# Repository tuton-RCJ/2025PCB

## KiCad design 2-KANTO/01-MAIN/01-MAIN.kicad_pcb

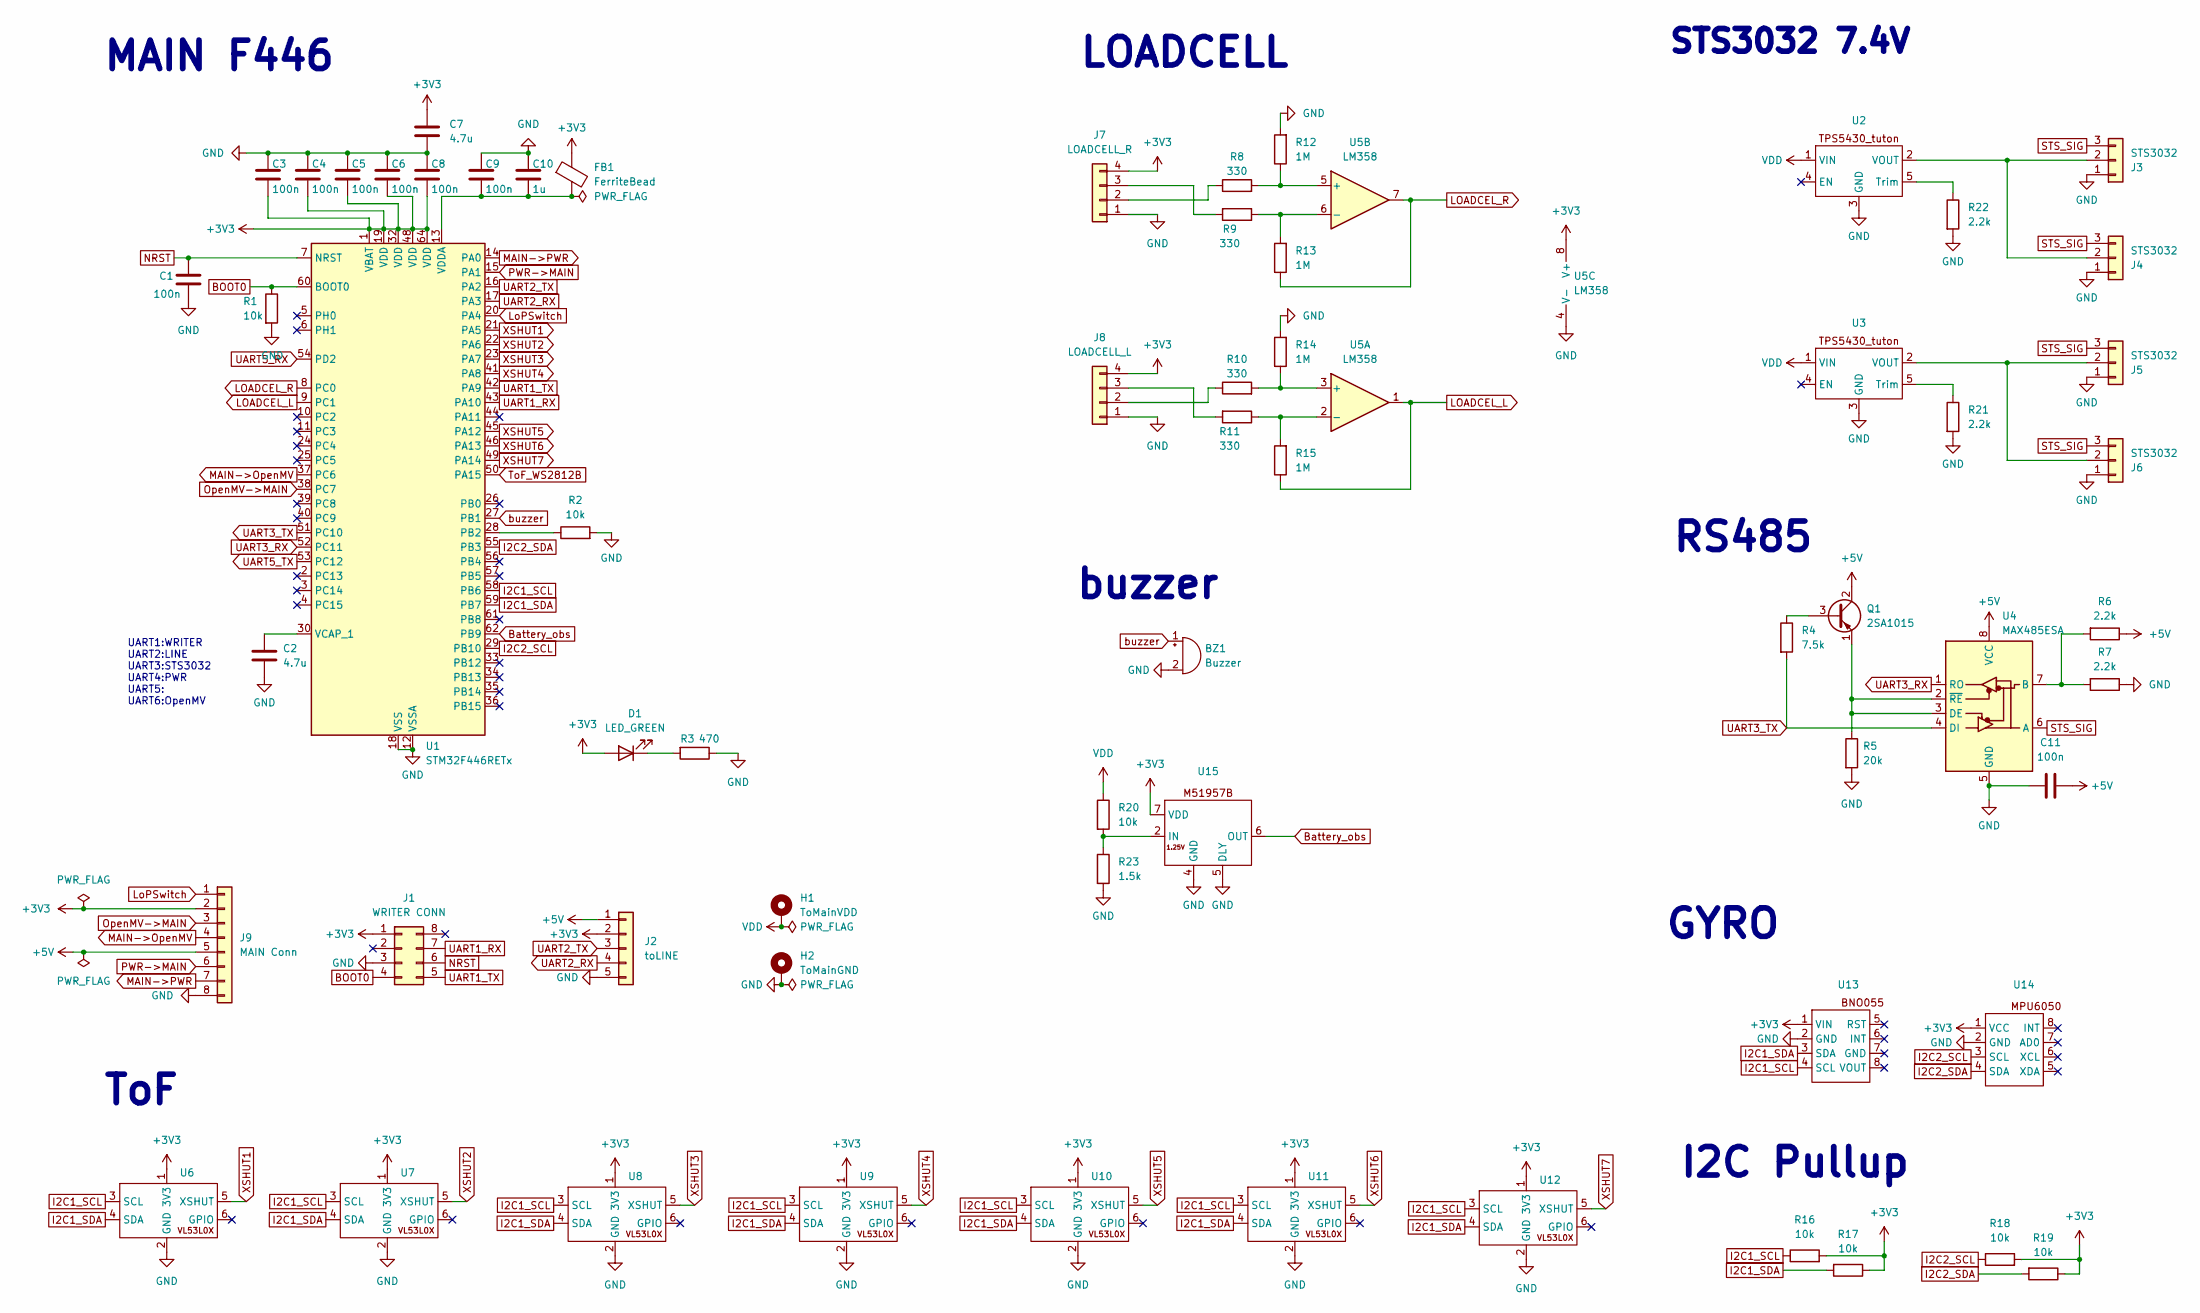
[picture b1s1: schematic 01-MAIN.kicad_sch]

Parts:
BZ1: Buzzer; Buzzer_TDK_PS1240P02BT_D12.2mm_H6.5mm
C1, C3, C4, C5, C6, C8, C9, C11: 100n; C_0402_1005Metric; LCSC C1525
C2, C7: 4.7u; C_0402_1005Metric; LCSC C23733
C10: 1u; C_0402_1005Metric; LCSC C52923
D1: LED_GREEN; LED_0805_2012Metric; LCSC C2297
FB1: FerriteBead; R_0805_2012Metric; LCSC C1015
H1: ToMainVDD; MountingHole_3.2mm_M3_Pad_Via
H2: ToMainGND; MountingHole_3.2mm_M3_Pad_Via
J1: WRITER CONN; PinSocket_2x04_P2.54mm_Horizontal
J2: toLINE; JST_XH_B5B-XH-A_1x05_P2.50mm_Vertical
J3, J4, J5, J6: STS3032; Molex_SPOX_5267-03A_1x03_P2.50mm_Vertical
J7: LOADCELL_R; JST_XH_B4B-XH-A_1x04_P2.50mm_Vertical
J8: LOADCELL_L; JST_XH_B4B-XH-A_1x04_P2.50mm_Vertical
J9: MAIN Conn; JST_XH_B8B-XH-A_1x08_P2.50mm_Vertical
Q1: 2SA1015; TO-92_Inline
R1, R2, R16, R17, R18, R19, R20: 10k; R_0603_1608Metric; LCSC C25804
R3: 470; R_0603_1608Metric; LCSC C23179
R4: 7.5k; R_0603_1608Metric; LCSC C23234
R5: 20k; R_0603_1608Metric; LCSC C4184
R6, R7, R21, R22: 2.2k; R_0603_1608Metric; LCSC C4190
R8, R9, R10, R11: 330; R_0603_1608Metric; LCSC C23138
R12, R13, R14, R15: 1M; R_0603_1608Metric; LCSC C22935
R23: 1.5k; R_0603_1608Metric; LCSC C22843
U1: STM32F446RETx; LQFP-64_10x10mm_P0.5mm; LCSC C69336
U2, U3: PinHeader_1x05_P2.54mm_Vertical
U4: MAX485ESA; SOP-8_3.9x4.9mm_P1.27mm; LCSC C668206
U5: LM358; SOIC-8_3.9x4.9mm_P1.27mm; LCSC C5423
U6, U7, U8, U9, U10, U11, U12: vl53l0x_vertical
U13: BNO055
U14: MPU6050
U15: M51957B

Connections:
+3V3: C3.2, C4.2, C5.2, C6.2, C7.1, C8.2, D1.2 (A), FB1.1, J1.1, J2.2, J7.4, J8.4, J9.2, R16.2, R17.1, R18.2, R19.1, U1.1 (VBAT), U1.19 (VDD), U1.32 (VDD), U1.48 (VDD), U1.64 (VDD), U5.8 (V+), U6.1 (3V3), U7.1 (3V3), U8.1 (3V3), U9.1 (3V3), U10.1 (3V3), U11.1 (3V3), U12.1 (3V3), U13.1 (VIN), U14.1 (VCC), U15.7 (VDD)
+5V: C11.1, J2.1, J9.5, Q1.2 (C), R6.1, U4.8 (VCC)
BOOT0: J1.4, R1.1, U1.60 (BOOT0)
Battery_obs: U1.62 (PB9), U15.6 (OUT)
GND: BZ1.2 (+), C1.1, C2.2, C3.1, C4.1, C5.1, C6.1, C7.2, C8.1, C9.1, C10.1, C11.2, H2.1, J1.3, J2.5, J3.1, J4.1, J5.1, J6.1, J7.1, J8.1, J9.8, R1.2, R2.2, R3.1, R5.2, R7.1, R12.2, R14.2, R21.2, R22.2, R23.2, U1.12 (VSSA), U1.18 (VSS), U1.31 (VSS), U1.47 (VSS), U1.63 (VSS), U2.3 (GND), U3.3 (GND), U4.5 (GND), U5.4 (V-), U6.2 (GND), U7.2 (GND), U8.2 (GND), U9.2 (GND), U10.2 (GND), U11.2 (GND), U12.2 (GND), U13.2 (GND), U14.2 (GND), U15.4 (GND), U15.5 (DLY)
I2C1_SCL: R16.1, U1.58 (PB6), U6.3 (SCL), U7.3 (SCL), U8.3 (SCL), U9.3 (SCL), U10.3 (SCL), U11.3 (SCL), U12.3 (SCL), U13.4 (SCL)
I2C1_SDA: R17.2, U1.59 (PB7), U6.4 (SDA), U7.4 (SDA), U8.4 (SDA), U9.4 (SDA), U10.4 (SDA), U11.4 (SDA), U12.4 (SDA), U13.3 (SDA)
I2C2_SCL: R18.1, U1.29 (PB10), U14.3 (SCL)
I2C2_SDA: R19.2, U1.55 (PB3), U14.4 (SDA)
LOADCEL_L: R15.1, U1.9 (PC1), U5.1
LOADCEL_R: R13.1, U1.8 (PC0), U5.7
LoPSwitch: J9.1, U1.20 (PA4)
MAIN->OpenMV: J9.4, U1.37 (PC6)
MAIN->PWR: J9.7, U1.14 (PA0)
NRST: C1.2, J1.6, U1.7 (NRST)
unnamed: D1.1 (K), R3.2
unnamed: J3.2, J4.2, U2.2 (VOUT)
unnamed: J5.2, J6.2, U3.2 (VOUT)
unnamed: J7.2, R8.1
unnamed: J7.3, R9.2
unnamed: J8.2, R10.1
unnamed: J8.3, R11.2
unnamed: Q1.3 (B), R4.1
unnamed: Q1.1 (E), R5.1, U4.2 (~RE), U4.3 (DE)
unnamed: R2.1, U1.28 (PB2)
unnamed: C2.1, U1.30 (VCAP_1)
unnamed: C9.2, C10.2, FB1.2, U1.13 (VDDA)
unnamed: R22.1, U2.5 (Trim)
unnamed: R21.1, U3.5 (Trim)
unnamed: R6.2, R7.2, U4.7 (B)
unnamed: R10.2, R14.1, U5.3 (+)
unnamed: R11.1, R15.2, U5.2 (-)
unnamed: R8.2, R12.1, U5.5 (+)
unnamed: R9.1, R13.2, U5.6 (-)
unnamed: R20.2, R23.1, U15.2 (IN)
OpenMV->MAIN: J9.3, U1.38 (PC7)
PWR->MAIN: J9.6, U1.15 (PA1)
STS_SIG: J3.3, J4.3, J5.3, J6.3, U4.6 (A)
ToF_WS2812B: U1.50 (PA15)
UART1_RX: J1.7, U1.43 (PA10)
UART1_TX: J1.5, U1.42 (PA9)
UART2_RX: J2.4, U1.17 (PA3)
UART2_TX: J2.3, U1.16 (PA2)
UART3_RX: U1.52 (PC11), U4.1 (RO)
UART3_TX: R4.2, U1.51 (PC10), U4.4 (DI)
UART5_RX: U1.54 (PD2)
UART5_TX: U1.53 (PC12)
VDD: H1.1, R20.1, U2.1 (VIN), U3.1 (VIN)
XSHUT1: U1.21 (PA5), U6.5 (XSHUT)
XSHUT2: U1.22 (PA6), U7.5 (XSHUT)
XSHUT3: U1.23 (PA7), U8.5 (XSHUT)
XSHUT4: U1.41 (PA8), U9.5 (XSHUT)
XSHUT5: U1.45 (PA12), U10.5 (XSHUT)
XSHUT6: U1.46 (PA13), U11.5 (XSHUT)
XSHUT7: U1.49 (PA14), U12.5 (XSHUT)
buzzer: BZ1.1 (-), U1.27 (PB1)

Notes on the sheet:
I2C Pullup
buzzer
RS485
ToF
MAIN F446
GYRO
STS3032 7.4V
LOADCELL
UART1:WRITER UART2:LINE UART3:STS3032 UART4:PWR UART5: UART6:OpenMV

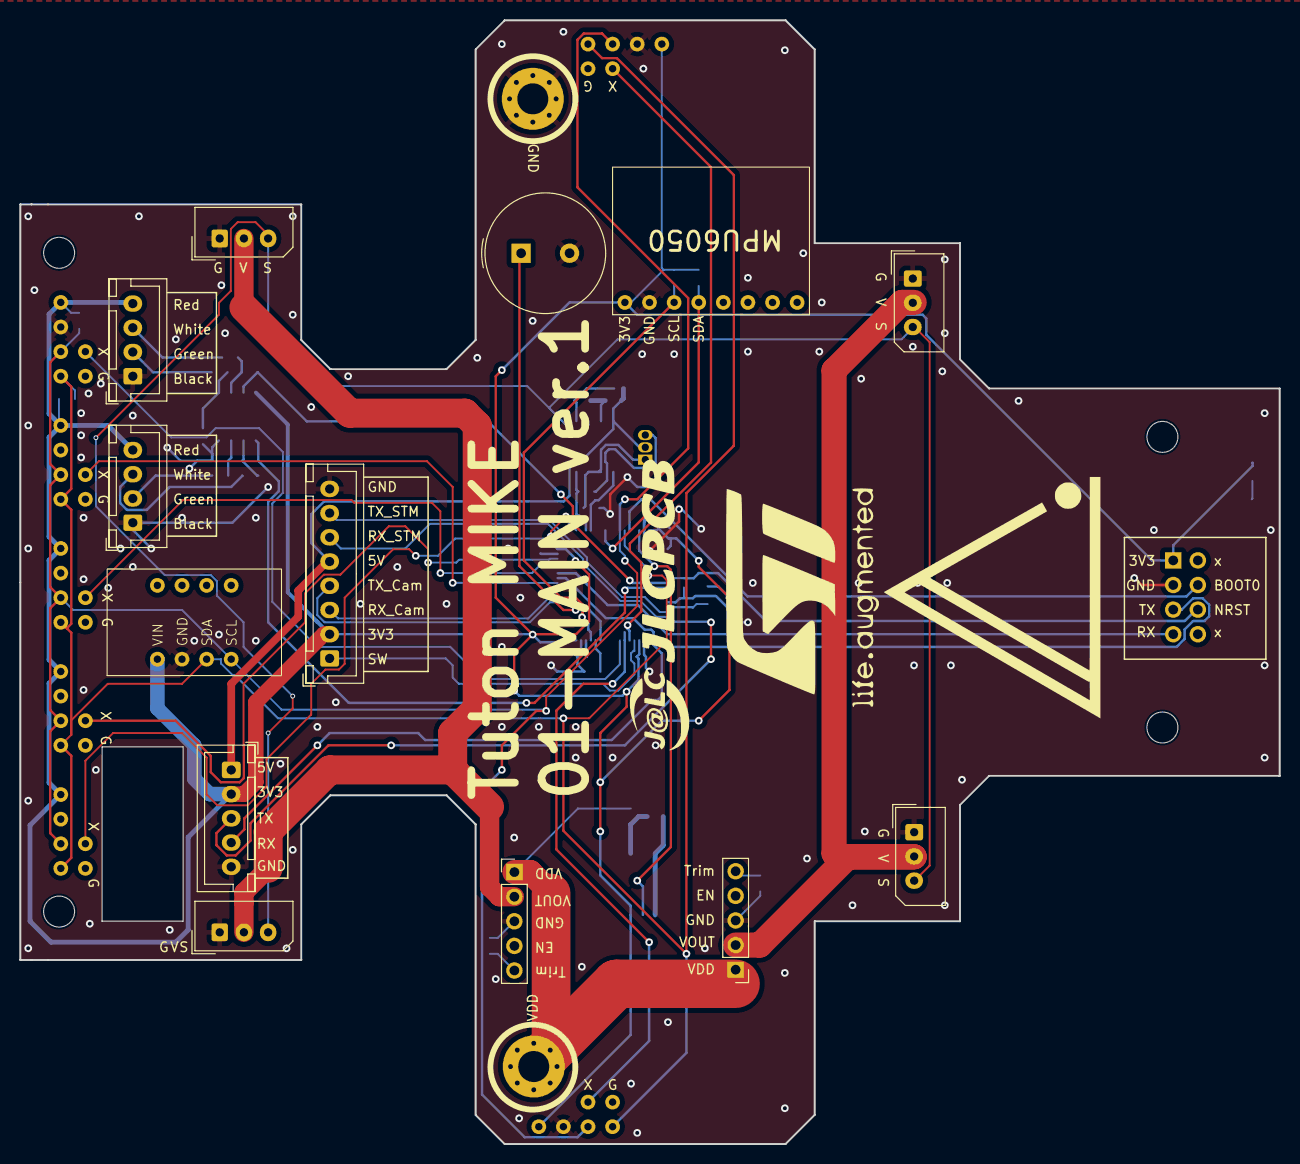
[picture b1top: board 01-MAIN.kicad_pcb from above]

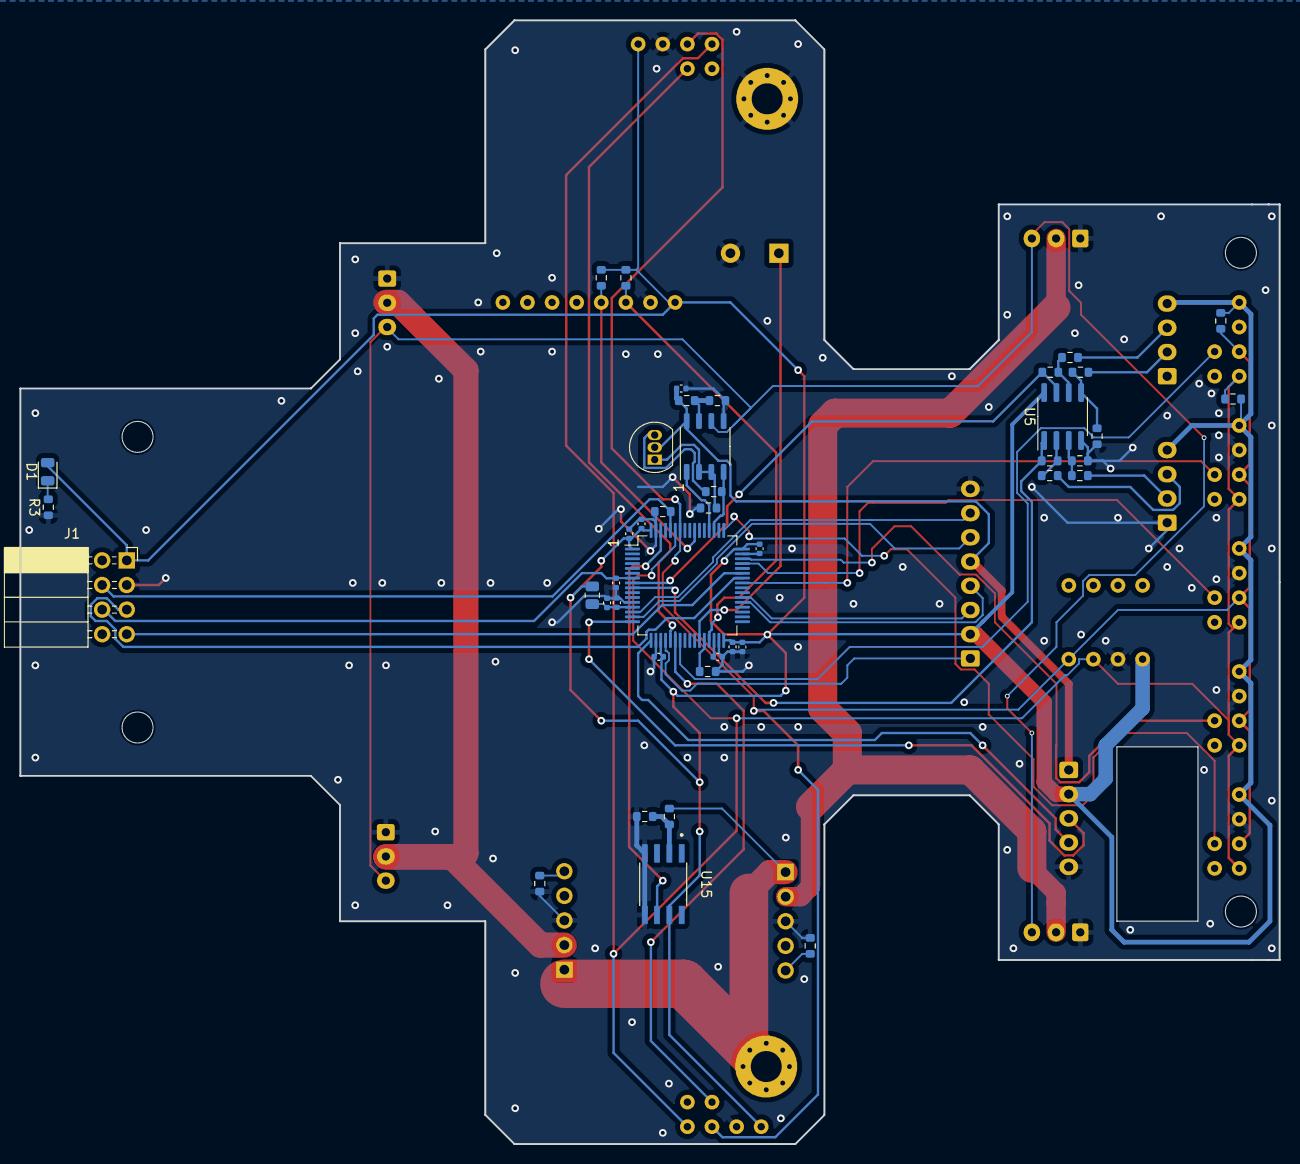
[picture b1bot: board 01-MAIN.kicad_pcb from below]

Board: 2 copper layers, 130.0 x 116.0 mm, 64 parts (42 on the bottom side), 53 nets.

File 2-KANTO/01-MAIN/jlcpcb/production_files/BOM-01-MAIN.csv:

Comment,Designator,Footprint,LCSC
FerriteBead,FB1,R_0805_2012Metric,C1015
100n,"C1,C11,C3,C4,C5,C6,C8,C9",C_0402_1005Metric,C1525
1.5k,R23,R_0603_1608Metric,C22843
1M,"R12,R13,R14,R15",R_0603_1608Metric,C22935
LED_GREEN,D1,LED_0805_2012Metric,C2297
330,"R10,R11,R8,R9",R_0603_1608Metric,C23138
470,R3,R_0603_1608Metric,C23179
7.5k,R4,R_0603_1608Metric,C23234
4.7u,"C2,C7",C_0402_1005Metric,C23733
10k,"R1,R16,R17,R18,R19,R2,R20",R_0603_1608Metric,C25804
20k,R5,R_0603_1608Metric,C4184
2.2k,"R21,R22,R6,R7",R_0603_1608Metric,C4190
1u,C10,C_0402_1005Metric,C52923
LM358,U5,SOIC-8_3.9x4.9mm_P1.27mm,C5423
MAX485ESA,U4,SOP-8_3.9x4.9mm_P1.27mm,C668206
STM32F446RETx,U1,LQFP-64_10x10mm_P0.5mm,C69336
toLINE,J2,JST_XH_B5B-XH-A_1x05_P2.50mm_Vertical,
LOADCELL_R,J7,JST_XH_B4B-XH-A_1x04_P2.50mm_Vertical,
~,U10,vl53l0x_vertical,
~,U14,MPU6050,
STS3032,J6,Molex_SPOX_5267-03A_1x03_P2.50mm_Vertical,
~,U6,vl53l0x_vertical,
~,U8,vl53l0x_vertical,
~,U7,vl53l0x_vertical,
STS3032,J3,Molex_SPOX_5267-03A_1x03_P2.50mm_Vertical,
~,U9,vl53l0x_vertical,
~,U13,BNO055,
LOADCELL_L,J8,JST_XH_B4B-XH-A_1x04_P2.50mm_Vertical,
Buzzer,BZ1,Buzzer_TDK_PS1240P02BT_D12.2mm_H6.5mm,
STS3032,J4,Molex_SPOX_5267-03A_1x03_P2.50mm_Vertical,
STS3032,J5,Molex_SPOX_5267-03A_1x03_P2.50mm_Vertical,
~,U11,vl53l0x_vertical,
~,U2,PinHeader_1x05_P2.54mm_Vertical,
~,U12,vl53l0x_vertical,
MAIN Conn,J9,JST_XH_B8B-XH-A_1x08_P2.50mm_Vertical,
~,U3,PinHeader_1x05_P2.54mm_Vertical,
2SA1015,Q1,TO-92_Inline,
~,U15,M51957B,
WRITER CONN,J1,PinSocket_2x04_P2.54mm_Horizontal,

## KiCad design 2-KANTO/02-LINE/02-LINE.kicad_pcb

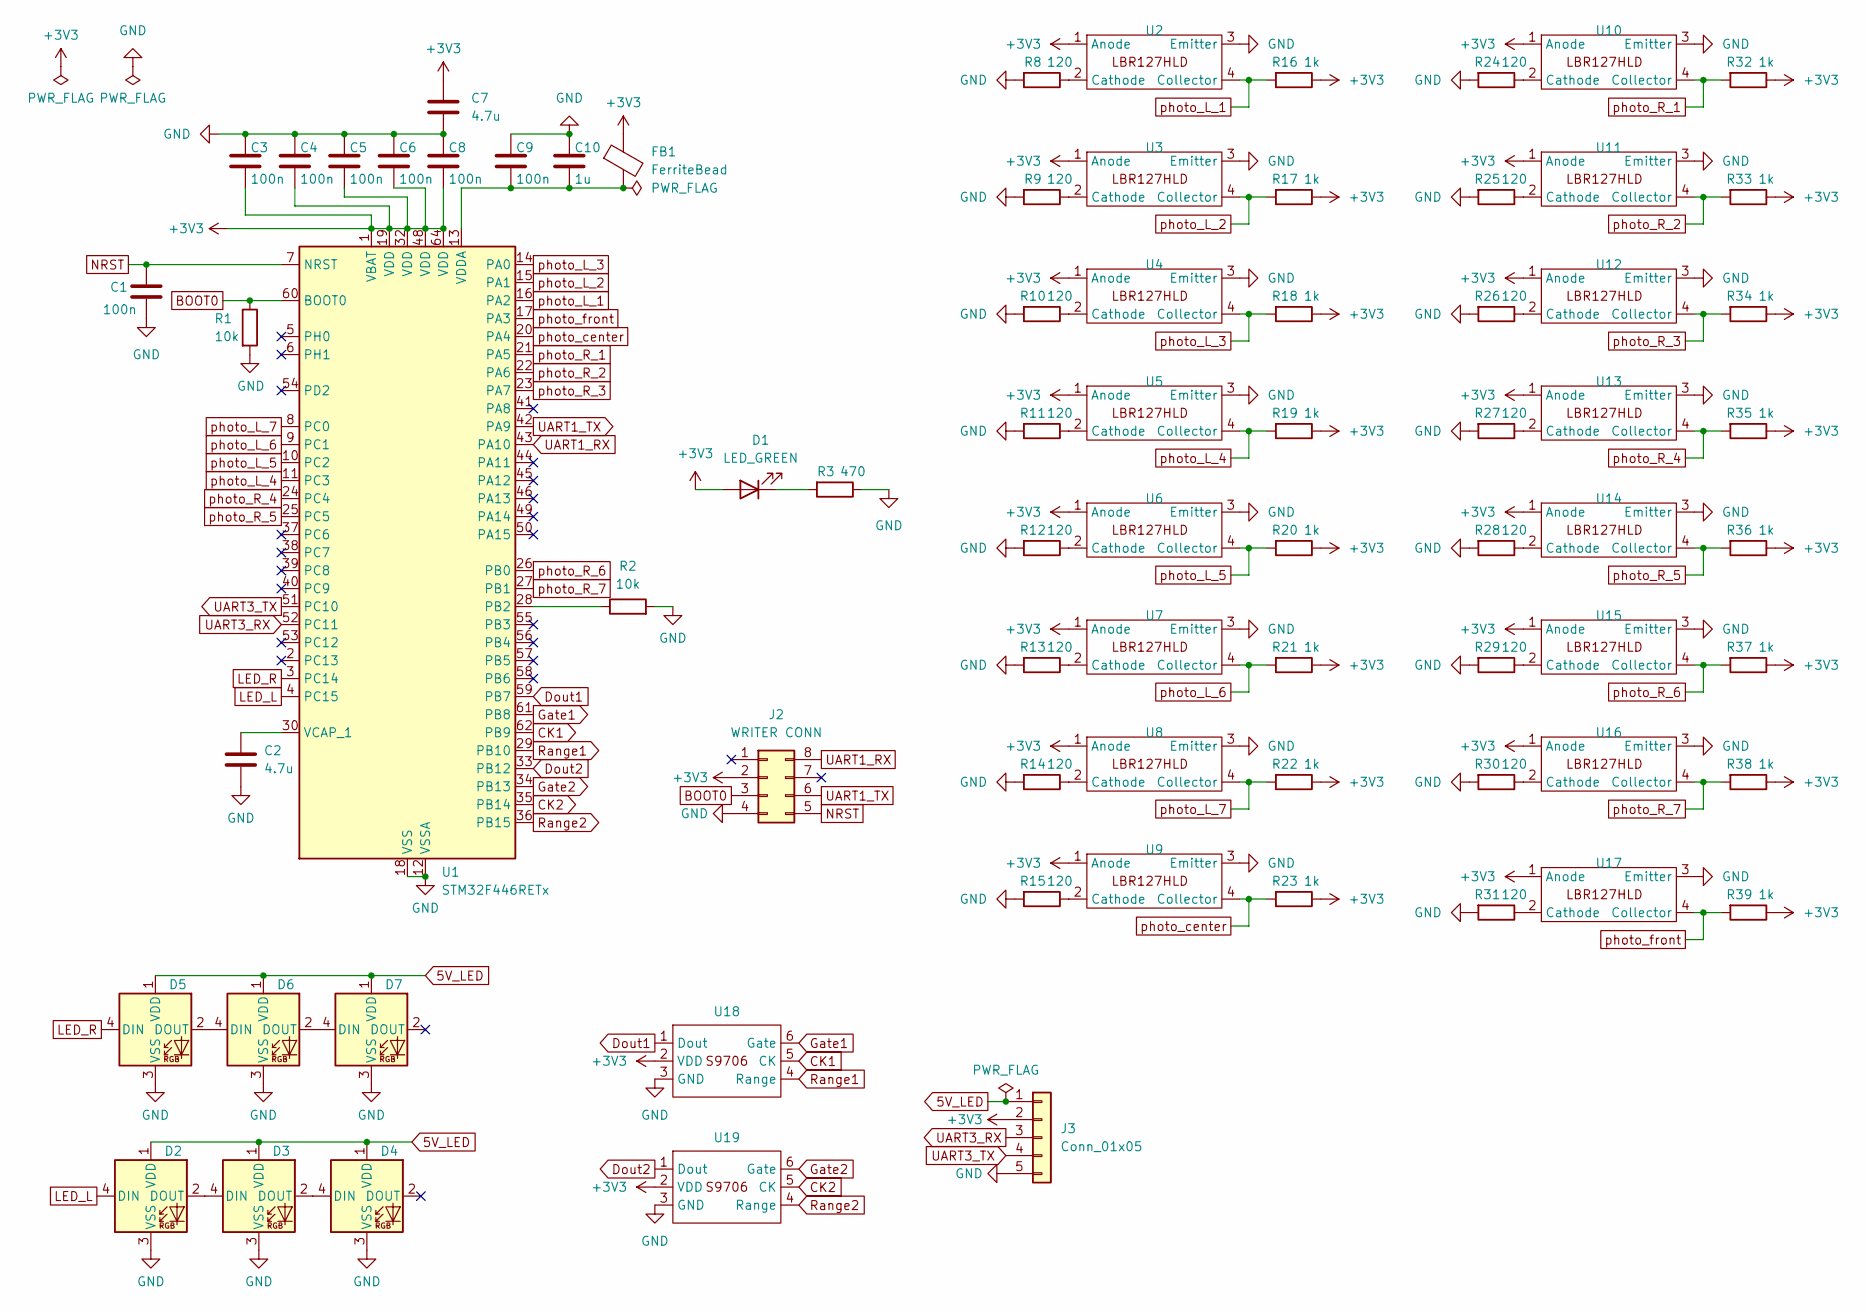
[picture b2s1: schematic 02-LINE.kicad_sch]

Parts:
C1, C3, C4, C5, C6, C8, C9: 100n; C_0402_1005Metric; LCSC C1525
C2, C7: 4.7u; C_0402_1005Metric; LCSC C23733
C10: 1u; C_0402_1005Metric; LCSC C52923
D1: LED_GREEN; LED_0805_2012Metric; LCSC C2297
D2, D3, D4, D5, D6, D7: WS2812B; LED_WS2812B_PLCC4_5.0x5.0mm_P3.2mm
FB1: FerriteBead; R_0805_2012Metric; LCSC C1015
J2: WRITER CONN; PinSocket_2x04_P2.54mm_Vertical
J3: Conn_01x05; JST_XH_B5B-XH-A_1x05_P2.50mm_Vertical
R1, R2: 10k; R_0603_1608Metric; LCSC C25804
R3: 470; R_0603_1608Metric; LCSC C23179
R8, R9, R10, R11, R12, R13, R14, R15, R24, R25, R26, R27, R28, R29, R30, R31: 120; R_0603_1608Metric; LCSC C22787
R16, R17, R18, R19, R20, R21, R22, R23, R32, R33, R34, R35, R36, R37, R38, R39: 1k; R_0603_1608Metric; LCSC C21190
U1: STM32F446RETx; LQFP-64_10x10mm_P0.5mm; LCSC C69336
U2, U3, U4, U5, U6, U7, U8, U9, U10, U11, U12, U13, U14, U15, U16, U17: LBR127HLD
U18, U19: S9706

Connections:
5V_LED: D2.1 (VDD), D3.1 (VDD), D4.1 (VDD), D5.1 (VDD), D6.1 (VDD), D7.1 (VDD), J3.1
+3V3: C3.2, C4.2, C5.2, C6.2, C7.1, C8.2, D1.2 (A), FB1.1, J2.2, J3.2, R16.1, R17.1, R18.1, R19.1, R20.1, R21.1, R22.1, R23.1, R32.1, R33.1, R34.1, R35.1, R36.1, R37.1, R38.1, R39.1, U1.1 (VBAT), U1.19 (VDD), U1.32 (VDD), U1.48 (VDD), U1.64 (VDD), U2.1 (Anode), U3.1 (Anode), U4.1 (Anode), U5.1 (Anode), U6.1 (Anode), U7.1 (Anode), U8.1 (Anode), U9.1 (Anode), U10.1 (Anode), U11.1 (Anode), U12.1 (Anode), U13.1 (Anode), U14.1 (Anode), U15.1 (Anode), U16.1 (Anode), U17.1 (Anode), U18.2 (VDD), U19.2 (VDD)
BOOT0: J2.3, R1.1, U1.60 (BOOT0)
CK1: U1.62 (PB9), U18.5 (CK)
CK2: U1.35 (PB14), U19.5 (CK)
Dout1: U1.59 (PB7), U18.1 (Dout)
Dout2: U1.33 (PB12), U19.1 (Dout)
GND: C1.1, C2.2, C3.1, C4.1, C5.1, C6.1, C7.2, C8.1, C9.1, C10.1, D2.3 (VSS), D3.3 (VSS), D4.3 (VSS), D5.3 (VSS), D6.3 (VSS), D7.3 (VSS), J2.4, J3.5, R1.2, R2.2, R3.1, R8.2, R9.2, R10.2, R11.2, R12.2, R13.2, R14.2, R15.2, R24.2, R25.2, R26.2, R27.2, R28.2, R29.2, R30.2, R31.2, U1.12 (VSSA), U1.18 (VSS), U1.31 (VSS), U1.47 (VSS), U1.63 (VSS), U2.3 (Emitter), U3.3 (Emitter), U4.3 (Emitter), U5.3 (Emitter), U6.3 (Emitter), U7.3 (Emitter), U8.3 (Emitter), U9.3 (Emitter), U10.3 (Emitter), U11.3 (Emitter), U12.3 (Emitter), U13.3 (Emitter), U14.3 (Emitter), U15.3 (Emitter), U16.3 (Emitter), U17.3 (Emitter), U18.3 (GND), U19.3 (GND)
Gate1: U1.61 (PB8), U18.6 (Gate)
Gate2: U1.34 (PB13), U19.6 (Gate)
LED_L: D2.4 (DIN), U1.4 (PC15)
LED_R: D5.4 (DIN), U1.3 (PC14)
NRST: C1.2, J2.5, U1.7 (NRST)
unnamed: D1.1 (K), R3.2
unnamed: D2.2 (DOUT), D3.4 (DIN)
unnamed: D3.2 (DOUT), D4.4 (DIN)
unnamed: D5.2 (DOUT), D6.4 (DIN)
unnamed: D6.2 (DOUT), D7.4 (DIN)
unnamed: R2.1, U1.28 (PB2)
unnamed: C2.1, U1.30 (VCAP_1)
unnamed: C9.2, C10.2, FB1.2, U1.13 (VDDA)
unnamed: R8.1, U2.2 (Cathode)
unnamed: R9.1, U3.2 (Cathode)
unnamed: R10.1, U4.2 (Cathode)
unnamed: R11.1, U5.2 (Cathode)
unnamed: R12.1, U6.2 (Cathode)
unnamed: R13.1, U7.2 (Cathode)
unnamed: R14.1, U8.2 (Cathode)
unnamed: R15.1, U9.2 (Cathode)
unnamed: R24.1, U10.2 (Cathode)
unnamed: R25.1, U11.2 (Cathode)
unnamed: R26.1, U12.2 (Cathode)
unnamed: R27.1, U13.2 (Cathode)
unnamed: R28.1, U14.2 (Cathode)
unnamed: R29.1, U15.2 (Cathode)
unnamed: R30.1, U16.2 (Cathode)
unnamed: R31.1, U17.2 (Cathode)
Range1: U1.29 (PB10), U18.4 (Range)
Range2: U1.36 (PB15), U19.4 (Range)
UART1_RX: J2.8, U1.43 (PA10)
UART1_TX: J2.6, U1.42 (PA9)
UART3_RX: J3.3, U1.52 (PC11)
UART3_TX: J3.4, U1.51 (PC10)
photo_L_1: R16.2, U1.16 (PA2), U2.4 (Collector)
photo_L_2: R17.2, U1.15 (PA1), U3.4 (Collector)
photo_L_3: R18.2, U1.14 (PA0), U4.4 (Collector)
photo_L_4: R19.2, U1.11 (PC3), U5.4 (Collector)
photo_L_5: R20.2, U1.10 (PC2), U6.4 (Collector)
photo_L_6: R21.2, U1.9 (PC1), U7.4 (Collector)
photo_L_7: R22.2, U1.8 (PC0), U8.4 (Collector)
photo_R_1: R32.2, U1.21 (PA5), U10.4 (Collector)
photo_R_2: R33.2, U1.22 (PA6), U11.4 (Collector)
photo_R_3: R34.2, U1.23 (PA7), U12.4 (Collector)
photo_R_4: R35.2, U1.24 (PC4), U13.4 (Collector)
photo_R_5: R36.2, U1.25 (PC5), U14.4 (Collector)
photo_R_6: R37.2, U1.26 (PB0), U15.4 (Collector)
photo_R_7: R38.2, U1.27 (PB1), U16.4 (Collector)
photo_center: R23.2, U1.20 (PA4), U9.4 (Collector)
photo_front: R39.2, U1.17 (PA3), U17.4 (Collector)

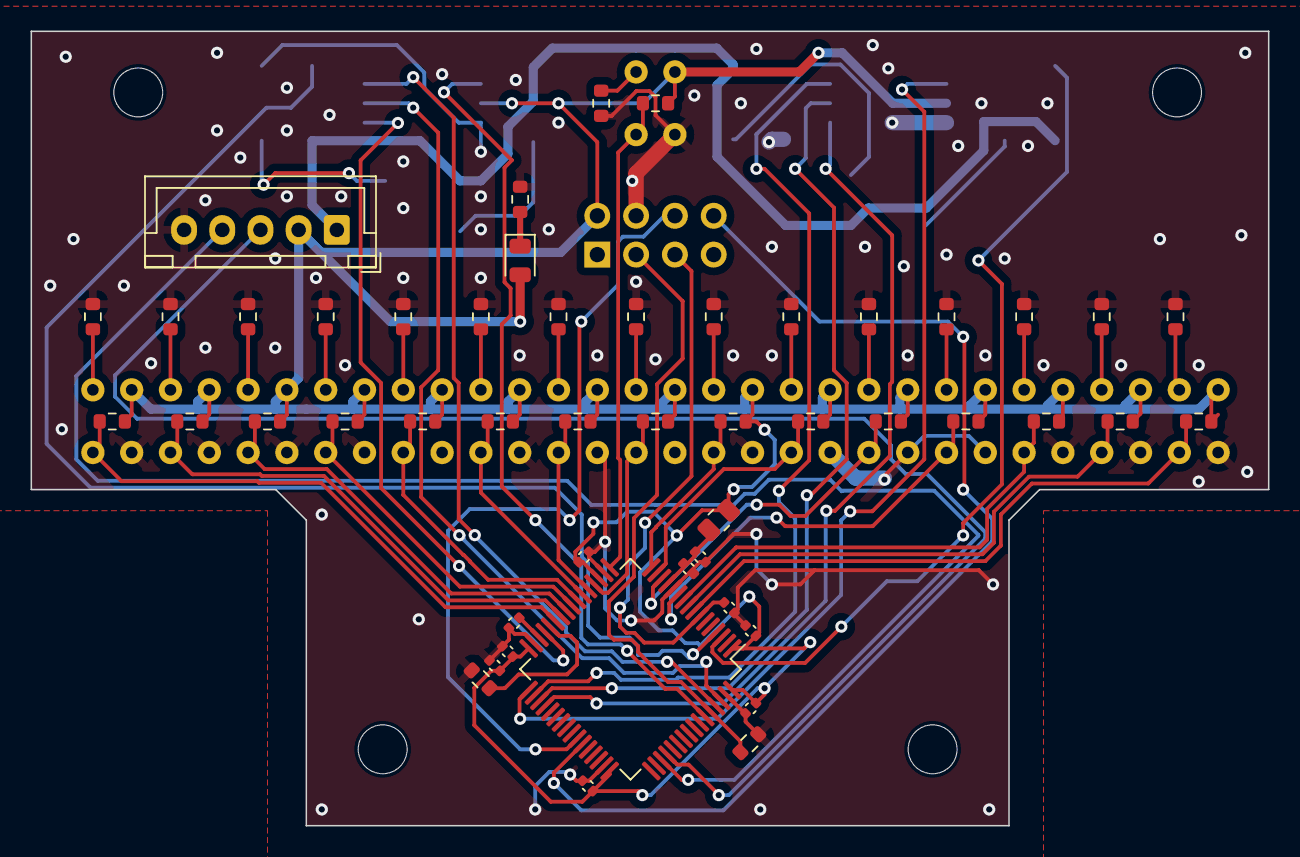
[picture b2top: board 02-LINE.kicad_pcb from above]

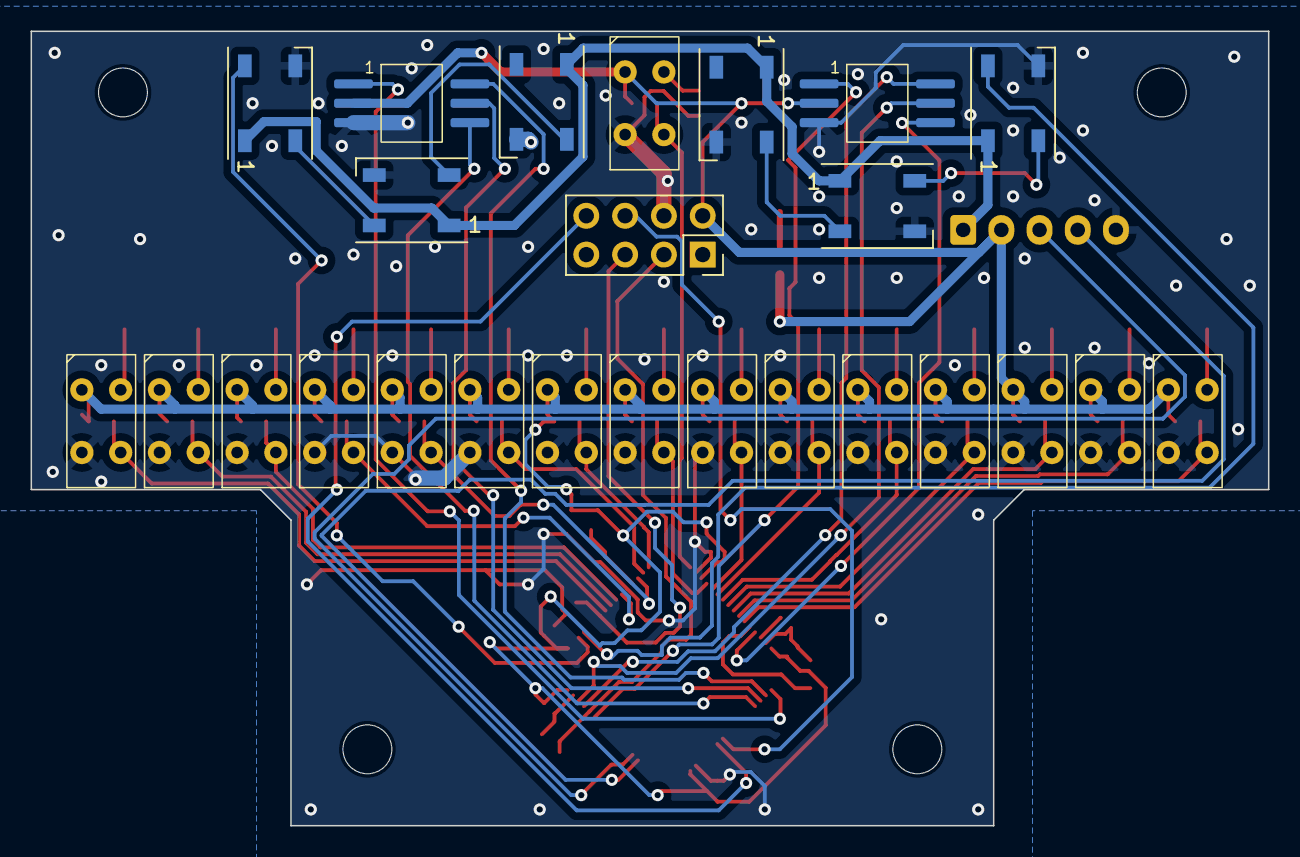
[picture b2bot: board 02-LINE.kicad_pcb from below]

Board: 2 copper layers, 81.0 x 52.0 mm, 74 parts (25 on the bottom side), 59 nets.

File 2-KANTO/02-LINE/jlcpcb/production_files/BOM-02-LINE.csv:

Comment,Designator,Footprint,LCSC
FerriteBead,FB1,R_0805_2012Metric,C1015
100n,"C1,C3,C4,C5,C6,C8,C9",C_0402_1005Metric,C1525
1k,"R16,R17,R18,R19,R20,R21,R22,R23,R32,R33,R34,R35,R36,R37,R38,R39",R_0603_1608Metric,C21190
120,"R10,R11,R12,R13,R14,R15,R24,R25,R26,R27,R28,R29,R30,R31,R8,R9",R_0603_1608Metric,C22787
LED_GREEN,D1,LED_0805_2012Metric,C2297
470,R3,R_0603_1608Metric,C23179
4.7u,"C2,C7",C_0402_1005Metric,C23733
10k,"R1,R2",R_0603_1608Metric,C25804
1u,C10,C_0402_1005Metric,C52923
STM32F446RETx,U1,LQFP-64_10x10mm_P0.5mm,C69336
Conn_01x05,J3,JST_XH_B5B-XH-A_1x05_P2.50mm_Vertical,
~,U16,LBR127HLD,
WS2812B,D5,LED_WS2812B_PLCC4_5.0x5.0mm_P3.2mm,
WS2812B,D6,LED_WS2812B_PLCC4_5.0x5.0mm_P3.2mm,
WS2812B,D4,LED_WS2812B_PLCC4_5.0x5.0mm_P3.2mm,
~,U17,LBR127HLD,
~,U7,LBR127HLD,
~,U6,LBR127HLD,
~,U3,LBR127HLD,
~,U9,LBR127HLD,
~,U12,LBR127HLD,
~,U8,LBR127HLD,
~,U10,LBR127HLD,
~,U5,LBR127HLD,
~,U14,LBR127HLD,
WS2812B,D3,LED_WS2812B_PLCC4_5.0x5.0mm_P3.2mm,
~,U2,LBR127HLD,
~,U13,LBR127HLD,
WS2812B,D2,LED_WS2812B_PLCC4_5.0x5.0mm_P3.2mm,
WS2812B,D7,LED_WS2812B_PLCC4_5.0x5.0mm_P3.2mm,
~,U11,LBR127HLD,
~,U4,LBR127HLD,
WRITER CONN,J2,PinSocket_2x04_P2.54mm_Vertical,
~,U15,LBR127HLD,
~,U19,S9706,
~,U18,S9706,

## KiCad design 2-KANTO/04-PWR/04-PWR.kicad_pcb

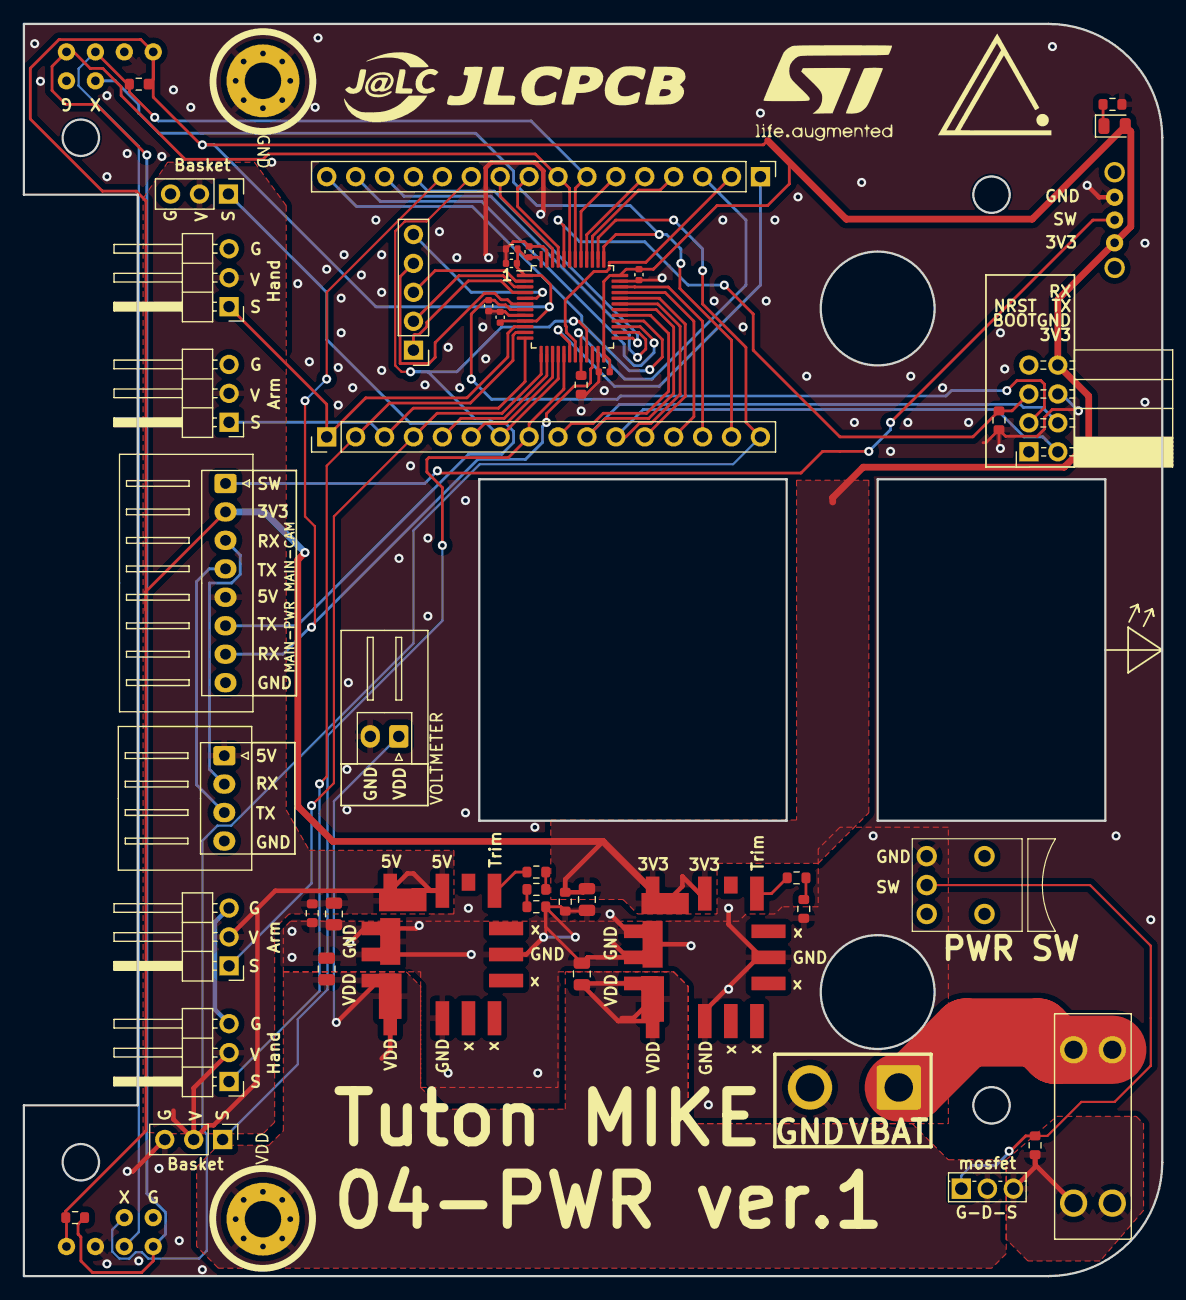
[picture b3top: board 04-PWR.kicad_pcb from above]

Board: 2 copper layers, 100.0 x 110.0 mm, 50 parts (0 on the bottom side), 55 nets.

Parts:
C1, C2, C3, C4, C5, C6: 100n; C_0402_1005Metric
C7: 4.7u; R_0402_1005Metric
C8, C9: 22uF; C_0805_2012Metric
C10, C11: 10uF; C_0805_2012Metric
D1: LED_GREEN; LED_0805_2012Metric
F1: Fuse; FUSE_3557-15
H1: ToMainVDD; MountingHole_3.2mm_M3_Pad_Via
H2: ToMainGND; MountingHole_3.2mm_M3_Pad_Via
J1: PB_PIN; PinHeader_1x16_P2.54mm_Vertical
J2: Conn_01x05; PinHeader_1x05_P2.54mm_Vertical
J3: PA_PIN; PinHeader_1x16_P2.54mm_Vertical
J4: WRITER CONN; PinSocket_2x04_P2.54mm_Horizontal
J5: MAIN Conn; JST_XH_S8B-XH-A_1x08_P2.50mm_Horizontal
J6: OpenMV Conn; JST_XH_S4B-XH-A_1x04_P2.50mm_Horizontal
J7: voltmeter; JST_XH_S2B-XH-A_1x02_P2.50mm_Horizontal
J8: Battery; SolderWire-2sqmm_1x02_P7.8mm_D2mm_OD3.9mm
M: ServoBasketRight; PinHeader_1x03_P2.54mm_Vertical
M1: ServoBasketLeft; PinHeader_1x03_P2.54mm_Vertical
M3: ServoArmLeft; PinHeader_1x03_P2.54mm_Horizontal
M4: ServoArmRight; PinHeader_1x03_P2.54mm_Horizontal
M5: ServoHandLeft; PinHeader_1x03_P2.54mm_Horizontal
M6: ServoHandRight; PinHeader_1x03_P2.54mm_Horizontal
Q1: Q_PMOS_GDS; TO-251-3_Vertical
R1, R2, R3, R4, R6: 10k; R_0603_1608Metric
R5: 470; R_0603_1608Metric
R7: 1k; R_0603_1608Metric
R8: 330; R_0603_1608Metric
R9: 10; R_0603_1608Metric
R10: 1.5k; R_0603_1608Metric
R11: 680; R_0603_1608Metric
R12, R13: 1.2k; R_0603_1608Metric
SW1: SW_SPDT; SK-12D11VG3
SW2: SW_SPST; AkizukiSmallRockerSwitchHorizontal
U1: STM32F103C8Tx; LQFP-48_7x7mm_P0.5mm
U2, U3: vl53l0x_vertical
U4, U5: OKL-T6-W12N-C-SMD

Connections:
+3V3: C1.1, C3.1, C4.1, C5.1, C6.1, C7.1, C10.1, D1.2 (A), J4.8, J5.2, R3.2, R4.1, R12.1, SW1.1 (A), U1.1 (VBAT), U1.9 (VDDA), U1.24 (VDD), U1.36 (VDD), U1.48 (VDD), U2.1 (3V3), U3.1 (3V3), U4.4 (Vout), U4.5 (Sense)
+5V: C11.1, J5.5, J6.1, M.2 (+), M1.2 (+), M3.2 (+), M4.2 (+), M5.2 (+), M6.2 (+), R13.1, U5.4 (Vout), U5.5 (Sense)
BOOT0: J4.5, R2.1, U1.44 (BOOT0)
GND: C1.2, C2.1, C3.2, C4.2, C5.2, C6.2, C7.2, C8.2, C9.2, C10.2, C11.2, H2.1, J4.6, J5.8, J6.4, J7.2, J8.2, M.3 (-), M1.3 (-), M3.3 (-), M4.3 (-), M5.3 (-), M6.3 (-), R1.1, R2.2, R5.1, R9.2, R11.2, R12.2, R13.2, SW1.3 (C), SW2.1 (A), U1.8 (VSSA), U1.23 (VSS), U1.35 (VSS), U1.47 (VSS), U2.2 (GND), U3.2 (GND), U4.1 (ON/OFF), U4.3 (GND), U4.7 (GND), U5.1 (ON/OFF), U5.3 (GND), U5.7 (GND)
LoPSwitch: J5.1, SW1.2 (B)
MAIN->OpenMV: J5.4, J6.3
MAIN->PWR: J1.12, J5.7, U1.22 (PB11)
NRST: C2.2, J4.3, U1.7 (NRST)
unnamed: D1.1 (K), R5.2
unnamed: J1.1, U1.18 (PB0)
unnamed: J1.2, U1.19 (PB1)
unnamed: J1.3, R1.2, U1.20 (PB2)
unnamed: J1.4, U1.39 (PB3)
unnamed: J1.5, U1.40 (PB4)
unnamed: J1.6, U1.41 (PB5)
unnamed: J1.9, U1.45 (PB8)
unnamed: J1.10, U1.46 (PB9)
unnamed: J1.13, U1.25 (PB12)
unnamed: J1.14, U1.26 (PB13)
unnamed: J1.15, U1.27 (PB14)
unnamed: J1.16, U1.28 (PB15)
unnamed: J2.1, U1.4 (PC15)
unnamed: J2.2, U1.3 (PC14)
unnamed: J2.3, U1.2 (PC13)
unnamed: J2.4, U1.6 (PD1)
unnamed: J2.5, U1.5 (PD0)
unnamed: J3.5, U1.14 (PA4)
unnamed: J3.6, U1.15 (PA5)
unnamed: J3.9, U1.29 (PA8)
unnamed: J3.12, U1.32 (PA11)
unnamed: J3.13, U1.33 (PA12)
unnamed: J3.14, U1.34 (PA13)
unnamed: F1.2, J8.1
unnamed: Q1.1 (G), R6.2, SW2.2 (B)
unnamed: F1.1, Q1.3 (S), R6.1
unnamed: R7.2, R8.1
unnamed: R8.2, R9.1
unnamed: R10.2, R11.1
unnamed: R10.1, U4.6 (Trim)
unnamed: R7.1, U5.6 (Trim)
OpenMV->MAIN: J5.3, J6.2
PWR->MAIN: J1.11, J5.6, U1.21 (PB10)
SCL: J1.7, R3.1, U1.42 (PB6), U2.3 (SCL), U3.3 (SCL)
SDA: J1.8, R4.2, U1.43 (PB7), U2.4 (SDA), U3.4 (SDA)
ServoArmLeft: J3.3, M3.1 (PWM), U1.12 (PA2)
ServoArmRight: J3.4, M4.1 (PWM), U1.13 (PA3)
ServoBasketLeft: J3.7, M1.1 (PWM), U1.16 (PA6)
ServoBasketRight: J3.8, M.1 (PWM), U1.17 (PA7)
ServoHandLeft: J3.1, M5.1 (PWM), U1.10 (PA0)
ServoHandRight: J3.2, M6.1 (PWM), U1.11 (PA1)
UART1_RX: J3.11, J4.2, U1.31 (PA10)
UART1_TX: J3.10, J4.4, U1.30 (PA9)
VDD: C8.1, C9.1, H1.1, J7.1, Q1.2 (D), U4.2 (Vin), U5.2 (Vin)
XSHUT1: J3.15, U1.37 (PA14), U2.5 (XSHUT)
XSHUT2: J3.16, U1.38 (PA15), U3.5 (XSHUT)

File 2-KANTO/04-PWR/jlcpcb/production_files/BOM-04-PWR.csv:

Comment,Designator,Footprint,LCSC
100n,"C1,C2,C3,C4,C5,C6",C_0402_1005Metric,C1525
10uF,"C10,C11",C_0805_2012Metric,C15850
1k,R7,R_0603_1608Metric,C21190
1.2k,"R12,R13",R_0603_1608Metric,C22765
1.5k,R10,R_0603_1608Metric,C22843
10,R9,R_0603_1608Metric,C22859
LED_GREEN,D1,LED_0805_2012Metric,C2297
330,R8,R_0603_1608Metric,C23138
470,R5,R_0603_1608Metric,C23179
680,R11,R_0603_1608Metric,C23228
4.7u,C7,R_0402_1005Metric,C23733
10k,"R1,R2,R3,R4,R6",R_0603_1608Metric,C25804
22uF,"C8,C9",C_0805_2012Metric,C45783
STM32F103C8Tx,U1,LQFP-48_7x7mm_P0.5mm,C8734
~,U5,OKL-T6-W12N-C-SMD,
SW_SPST,SW2,AkizukiSmallRockerSwitchHorizontal,
~,U4,OKL-T6-W12N-C-SMD,
MAIN Conn,J5,JST_XH_S8B-XH-A_1x08_P2.50mm_Horizontal,
ServoHandRight,M6,PinHeader_1x03_P2.54mm_Horizontal,
Fuse,F1,FUSE_3557-15,
~,U2,vl53l0x_vertical,
WRITER CONN,J4,PinSocket_2x04_P2.54mm_Horizontal,
~,U3,vl53l0x_vertical,
Conn_01x05,J2,PinHeader_1x05_P2.54mm_Vertical,
ServoArmRight,M4,PinHeader_1x03_P2.54mm_Horizontal,
ServoHandLeft,M5,PinHeader_1x03_P2.54mm_Horizontal,
voltmeter,J7,JST_XH_S2B-XH-A_1x02_P2.50mm_Horizontal,
OpenMV Conn,J6,JST_XH_S4B-XH-A_1x04_P2.50mm_Horizontal,
Q_PMOS_GDS,Q1,TO-251-3_Vertical,
PA_PIN,J3,PinHeader_1x16_P2.54mm_Vertical,
ServoArmLeft,M3,PinHeader_1x03_P2.54mm_Horizontal,
PB_PIN,J1,PinHeader_1x16_P2.54mm_Vertical,
SW_SPDT,SW1,SK-12D11VG3,
ServoBasketLeft,M1,PinHeader_1x03_P2.54mm_Vertical,
